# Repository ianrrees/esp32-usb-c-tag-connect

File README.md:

# ESP32 USB Development Tool

This board adapts USB (either a type-C socket or a cable) to a Tag Connect
TC2030-compatible footprint, for use with ESP32 such as ESP32-S3 that provide
on-chip USB JTAG and UART functionality.  The Tag Connect footprint is
compatible with the
[TC2030-USB](https://www.tag-connect.com/product/tc2030-usb), replacing the two
N/C pins in that footprint with EN and IO0, used for reset and bootloader
buttons.

## Pinouts

| J2     |      | Tag Connect header                           |
|--------|------|----------------------------------------------|
| 1      | VBUS | USB VBUS +5V                                 |
| 2      | IO0  | Hold low during reset to stay in bootloader  |
| 3      | D-   | USB data                                     |
| 4      | D+   | USB data                                     |
| 5      | GND  | Ground                                       |
| 6      | EN   | Pull low to reset the ESP32                  |

| J3 | USB cable termination |
|----|-----------------------|
| 1  | GND                   |
| 2  | D+                    |
| 3  | D-                    |
| 4  | VBUS                  |

## BOM

| Qty          | Refdes            | Description                                |
|--------------|-------------------|--------------------------------------------|
| 1            |                   | PCB - [available from PCBWay](https://www.pcbway.com/project/shareproject/USB_C_to_Tag_Connect_TC2030_for_ESP32_USB_debugging_v1_5e1c53b1.html) |
| 1 (optional) | J1                | aliexpress 16-pin USB-C connector          |
| 2            | Reset, Bootloader | aliexpress 6x6x5 SMD tactile button switch |
| 2            | R3, R4            | 0603 0 Ohm                                 |
| 2            | R1, R2            | 0603 1.5k Ohm                              |
| 1            | J2                | 2x6 0.1" box header                        |

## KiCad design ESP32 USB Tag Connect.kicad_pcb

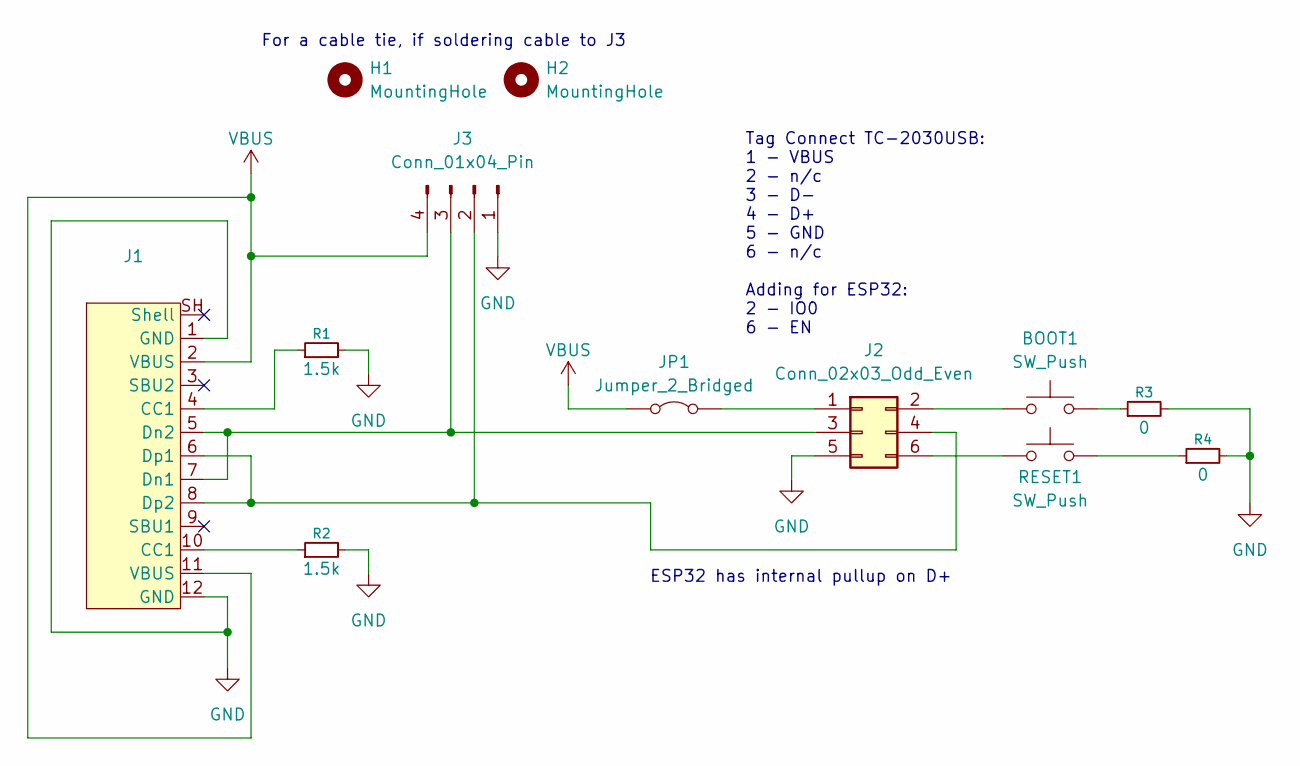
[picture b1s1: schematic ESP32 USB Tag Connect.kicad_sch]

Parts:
BOOT1: SW_Push; SW_Push_1P1T_NO_E-Switch_TL3301NxxxxxG
H1, H2: MountingHole; MountingHole_3mm
J1: USB-C 16 pin socket
J2: Conn_02x03_Odd_Even; IDC-Header_2x03_P2.54mm_Vertical
J3: Conn_01x04_Pin; PinHeader_1x04_P2.54mm_Vertical
JP1: Jumper_2_Bridged; SolderJumper-2_P1.3mm_Bridged_RoundedPad1.0x1.5mm
R1, R2: 1.5k; R_0603_1608Metric_Pad0.98x0.95mm_HandSolder
R3, R4: 0; R_0603_1608Metric_Pad0.98x0.95mm_HandSolder
RESET1: SW_Push; SW_Push_1P1T_NO_E-Switch_TL3301NxxxxxG

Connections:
GND: J1.1 (GND), J1.12 (GND), J2.5, J3.1, R1.2, R2.2, R3.2, R4.2
unnamed: BOOT1.2, R3.1
unnamed: J1.4 (CC1), R1.1
unnamed: J1.10 (CC1), R2.1
unnamed: J1.5 (Dn2), J1.7 (Dn1), J2.3, J3.3
unnamed: J1.6 (Dp1), J1.8 (Dp2), J2.4, J3.2
unnamed: J2.1, JP1.2 (B)
unnamed: BOOT1.1, J2.2
unnamed: J2.6, RESET1.1
unnamed: R4.1, RESET1.2
VBUS: J1.2 (VBUS), J1.11 (VBUS), J3.4, JP1.1 (A)

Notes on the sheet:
ESP32 has internal pullup on D+
Tag Connect TC-2030USB: 1 - VBUS 2 - n/c 3 - D- 4 - D+ 5 - GND 6 - n/c Adding for ESP32: 2 - IO0 6 - EN
For a cable tie, if soldering cable to J3

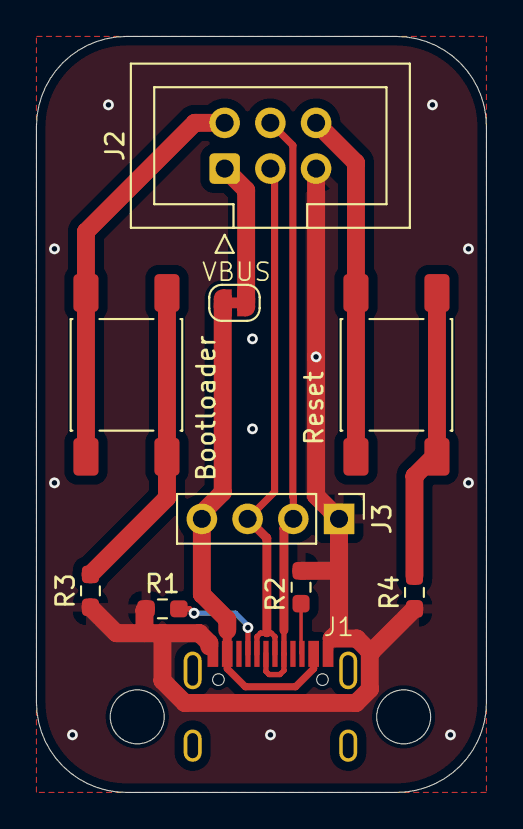
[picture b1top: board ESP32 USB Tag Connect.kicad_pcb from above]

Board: 2 copper layers, 25.0 x 42.0 mm, 12 parts (0 on the bottom side), 11 nets.

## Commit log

2025-07-17 V1 design
2025-07-31 Add photo, expand README.md
